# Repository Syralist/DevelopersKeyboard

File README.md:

# DevelopersKeyboard
An Arduino based keyboard for software developers.

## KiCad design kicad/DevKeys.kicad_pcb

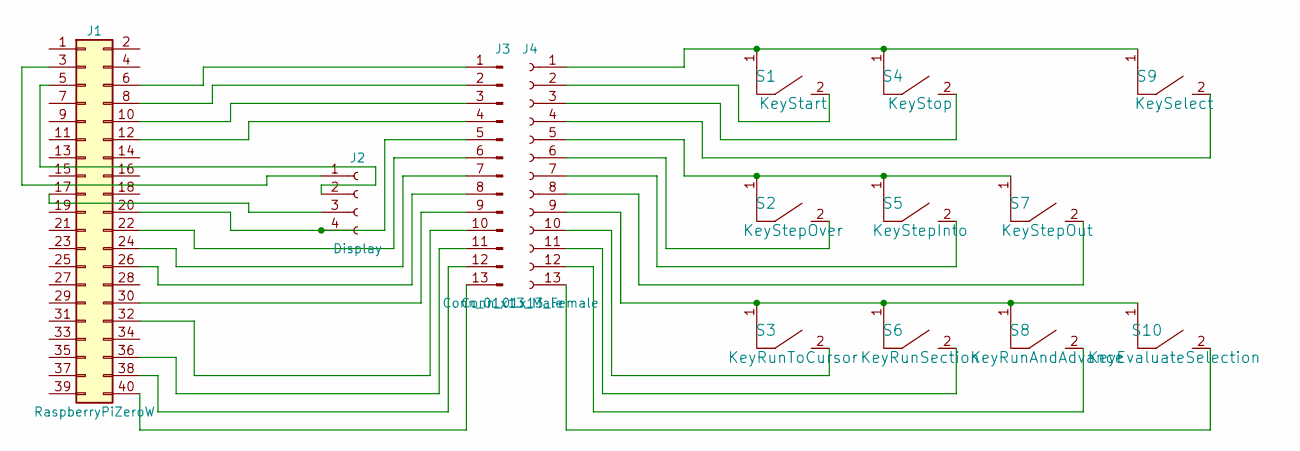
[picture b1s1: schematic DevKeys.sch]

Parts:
J1: RaspberryPiZeroW; Pin_Header_Straight_2x20_Pitch2.54mm
J2: Display; Socket_Strip_Straight_1x04_Pitch2.54mm
J3: Conn_01x13_Male; Pin_Header_Angled_1x13_Pitch2.54mm
J4: Conn_01x13_Female; Pin_Header_Straight_1x13_Pitch2.54mm
S1: KeyStart; MX1A
S2: KeyStepOver; MX1A
S3: KeyRunToCursor; MX1A
S4: KeyStop; MX1A
S5: KeyStepInto; MX1A
S6: KeyRunSection; MX1A
S7: KeyStepOut; MX1A
S8: KeyRunAndAdvance; MX1A
S9: KeySelect; MX1A
S10: KeyEvaluateSelection; MX1A

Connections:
unnamed: J1.3, J2.1
unnamed: J1.5, J2.2
unnamed: J1.6, J3.1
unnamed: J1.8, J3.2
unnamed: J1.10, J3.3
unnamed: J1.12, J3.4
unnamed: J1.17, J2.3
unnamed: J1.20, J2.4, J3.5
unnamed: J1.22, J3.6
unnamed: J1.24, J3.7
unnamed: J1.26, J3.8
unnamed: J1.30, J3.9
unnamed: J1.32, J3.10
unnamed: J1.36, J3.11
unnamed: J1.38, J3.12
unnamed: J1.40, J3.13
unnamed: J4.1, S1.1, S4.1, S9.1
unnamed: J4.2, S1.2
unnamed: J4.3, S4.2
unnamed: J4.4, S9.2
unnamed: J4.5, S2.1, S5.1, S7.1
unnamed: J4.6, S2.2
unnamed: J4.7, S5.2
unnamed: J4.8, S7.2
unnamed: J4.9, S3.1, S6.1, S8.1, S10.1
unnamed: J4.10, S3.2
unnamed: J4.11, S6.2
unnamed: J4.12, S8.2
unnamed: J4.13, S10.2

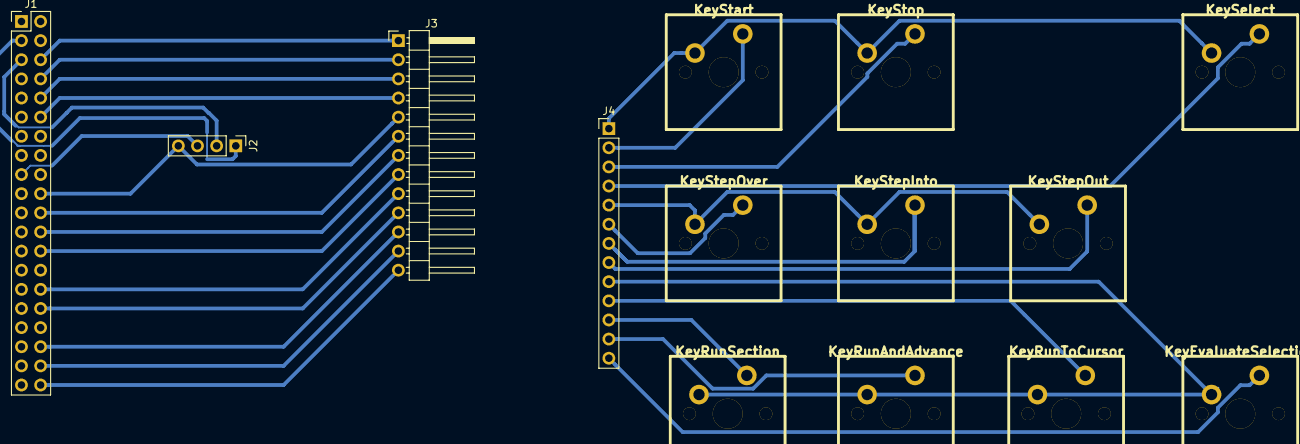
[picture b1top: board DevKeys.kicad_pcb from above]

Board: 2 copper layers, 14 parts (0 on the bottom side), 29 nets.

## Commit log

2016-08-15 added .gitignore and .gitmodules
2016-08-15 added arudino libs submodule
2016-08-15 added kicad to .gitignore
2016-08-15 first iteration PCB
2016-08-17 dioden vor den Tasten entfernt
2016-09-24 finished layout for first prototype pcb
2017-02-12 updated to new lib
2018-01-21 Links zum Thema UsbGadget
2018-01-27 added setup script
2018-01-27 proof of concept erfolgreich
2018-01-27 zwischenstand 27.01.18
2018-02-03 Klasse KeycodeSender fertig
2018-02-03 Bugfix: Device zum schreiben
2018-02-11 Keycaps für Start und Stopp. Signed-off-by: Thomas Helmke <thomas.helmke@gmx.de>
2018-02-28 share zu .gitignore hinzugefügt
2018-02-28 jetzt alle send methoden mit modifier
2018-02-28 neues Platinen-Layout
2018-03-24 Layout angepasst zum ätzen.
2018-03-24 neuer Testcode für fertige Platine
2018-03-24 Pin-Nummern im Buttontest angepasst
2018-03-24 noch ein fix für die button nummerierung
2018-03-29 erster test mit oled display
2018-03-30 Icons für die Aktionen.
2018-03-30 oled test mit bildern
2018-03-30 angefangen alles zusammenzufügen
2018-03-31 alle Funktionen programmiert
2018-04-07 aktuelles Verzeichnis wechseln
2018-04-07 Gehäuse angefangen
